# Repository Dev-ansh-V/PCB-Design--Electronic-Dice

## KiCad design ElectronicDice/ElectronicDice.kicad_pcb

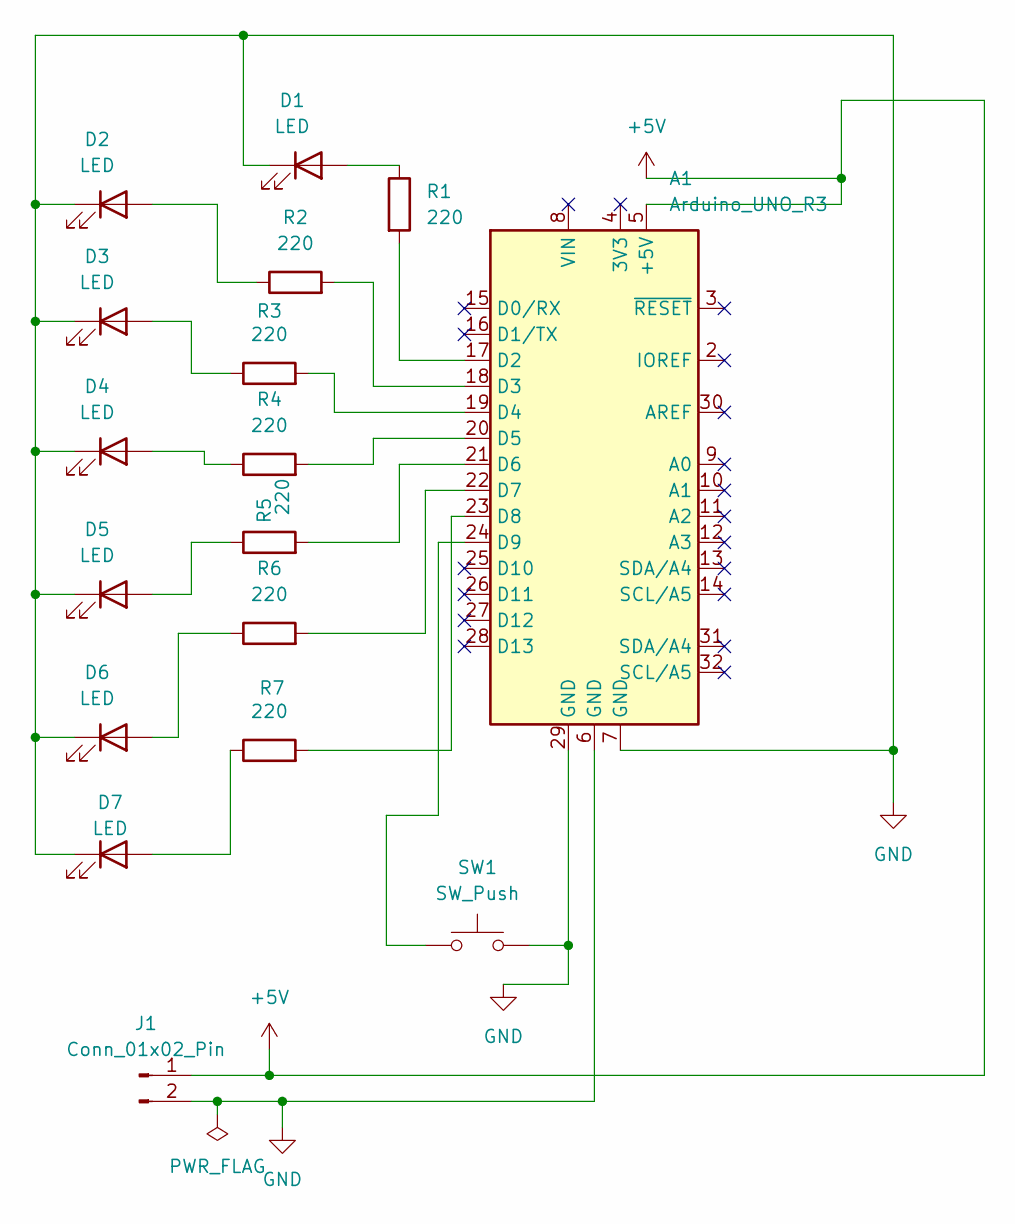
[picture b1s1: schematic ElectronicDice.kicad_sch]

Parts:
A1: Arduino_UNO_R3
D1, D2, D3, D4, D5, D6, D7: LED; LED_D5.0mm
J1: Conn_01x02_Pin; PinHeader_1x02_P2.54mm_Vertical
R1, R2, R3, R4, R5, R6, R7: 220; R_Axial_DIN0207_L6.3mm_D2.5mm_P10.16mm_Horizontal
SW1: SW_Push; SW_PUSH_6mm

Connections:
+5V: A1.5 (+5V), J1.1
GND: A1.6 (GND), A1.7 (GND), A1.29 (GND), D1.1 (K), D2.1 (K), D3.1 (K), D4.1 (K), D5.1 (K), D6.1 (K), D7.1 (K), J1.2, SW1.2
unnamed: A1.17 (D2), R1.2
unnamed: A1.18 (D3), R2.2
unnamed: A1.19 (D4), R3.2
unnamed: A1.20 (D5), R4.2
unnamed: A1.21 (D6), R5.2
unnamed: A1.22 (D7), R6.2
unnamed: A1.23 (D8), R7.2
unnamed: A1.24 (D9), SW1.1
unnamed: D1.2 (A), R1.1
unnamed: D2.2 (A), R2.1
unnamed: D3.2 (A), R3.1
unnamed: D4.2 (A), R4.1
unnamed: D5.2 (A), R5.1
unnamed: D6.2 (A), R6.1
unnamed: D7.2 (A), R7.1

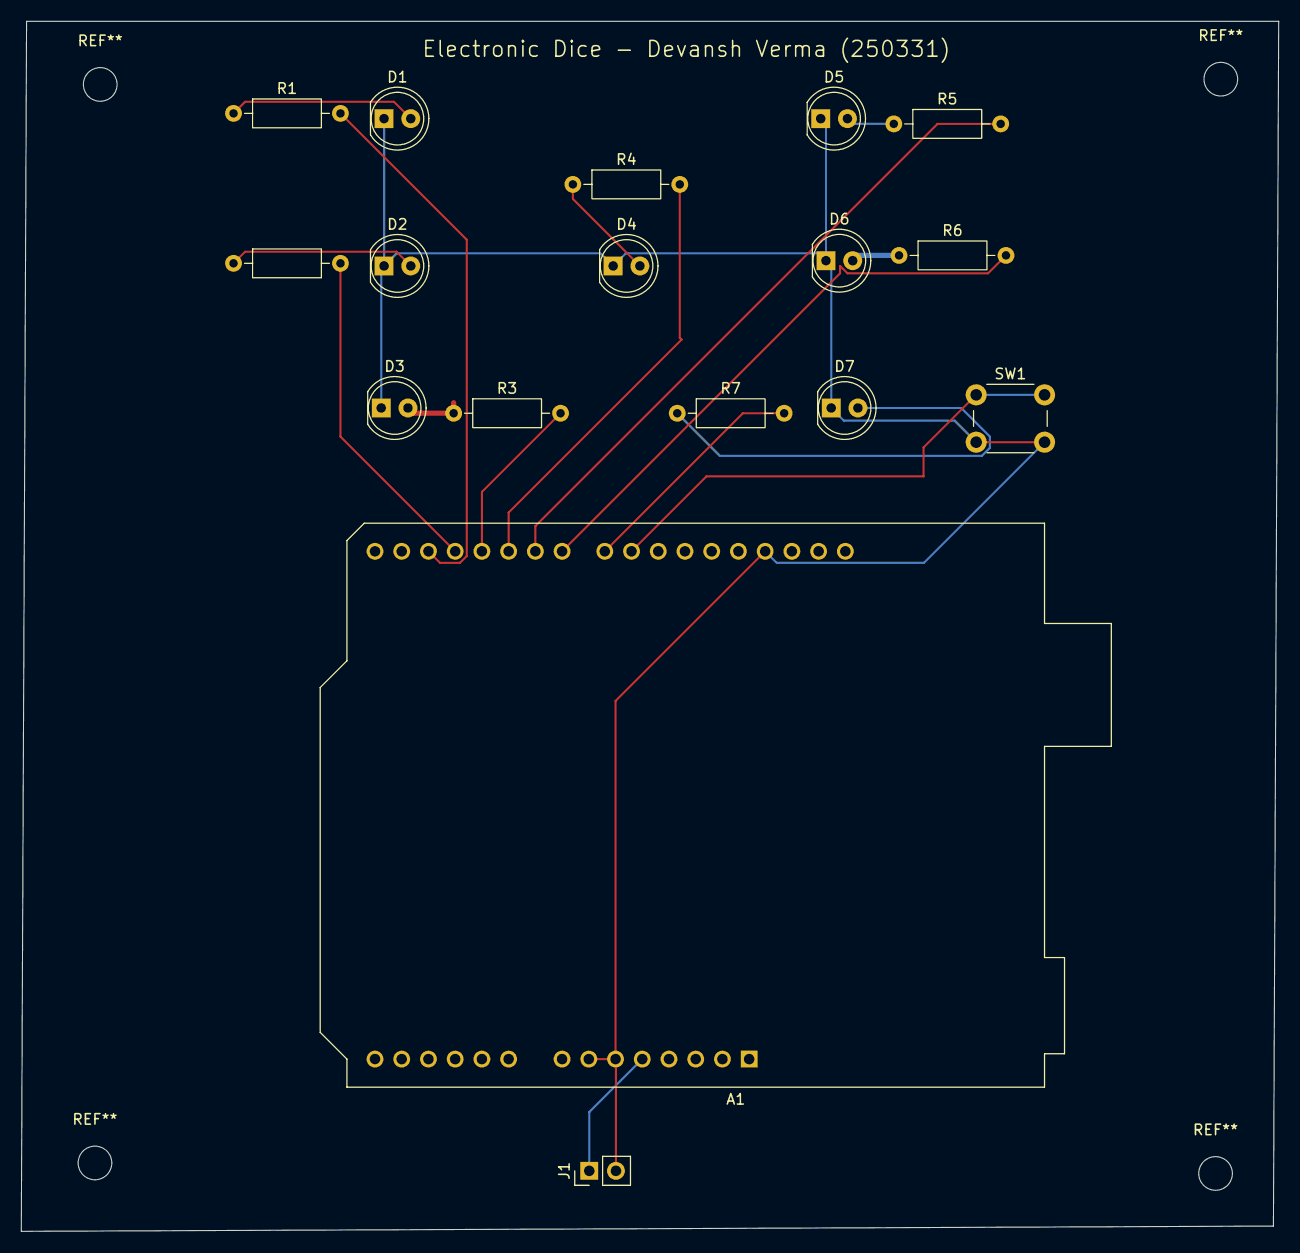
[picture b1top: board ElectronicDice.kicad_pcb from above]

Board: 2 copper layers, 119.5 x 115.0 mm, 17 parts (0 on the bottom side), 17 nets.

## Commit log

2026-05-19 making initial circuit
2026-05-19 Assigned Footprints
2026-05-19 Ran ECR and fixed the errors with the circuit
2026-05-23 Arranged components in PCB editor
2026-05-23 Added connections in PCB
2026-05-23 PCB design completed
2026-05-23 added the gerber and pdfs
2026-05-23 organised the files properly
2026-05-24 added minor aesthetic changes to pcb
2026-05-24 added an image of the 3D model of the PCB
2026-05-24 added explanation
2026-05-24 updated the name of the folder to meet the deliverable criteria
